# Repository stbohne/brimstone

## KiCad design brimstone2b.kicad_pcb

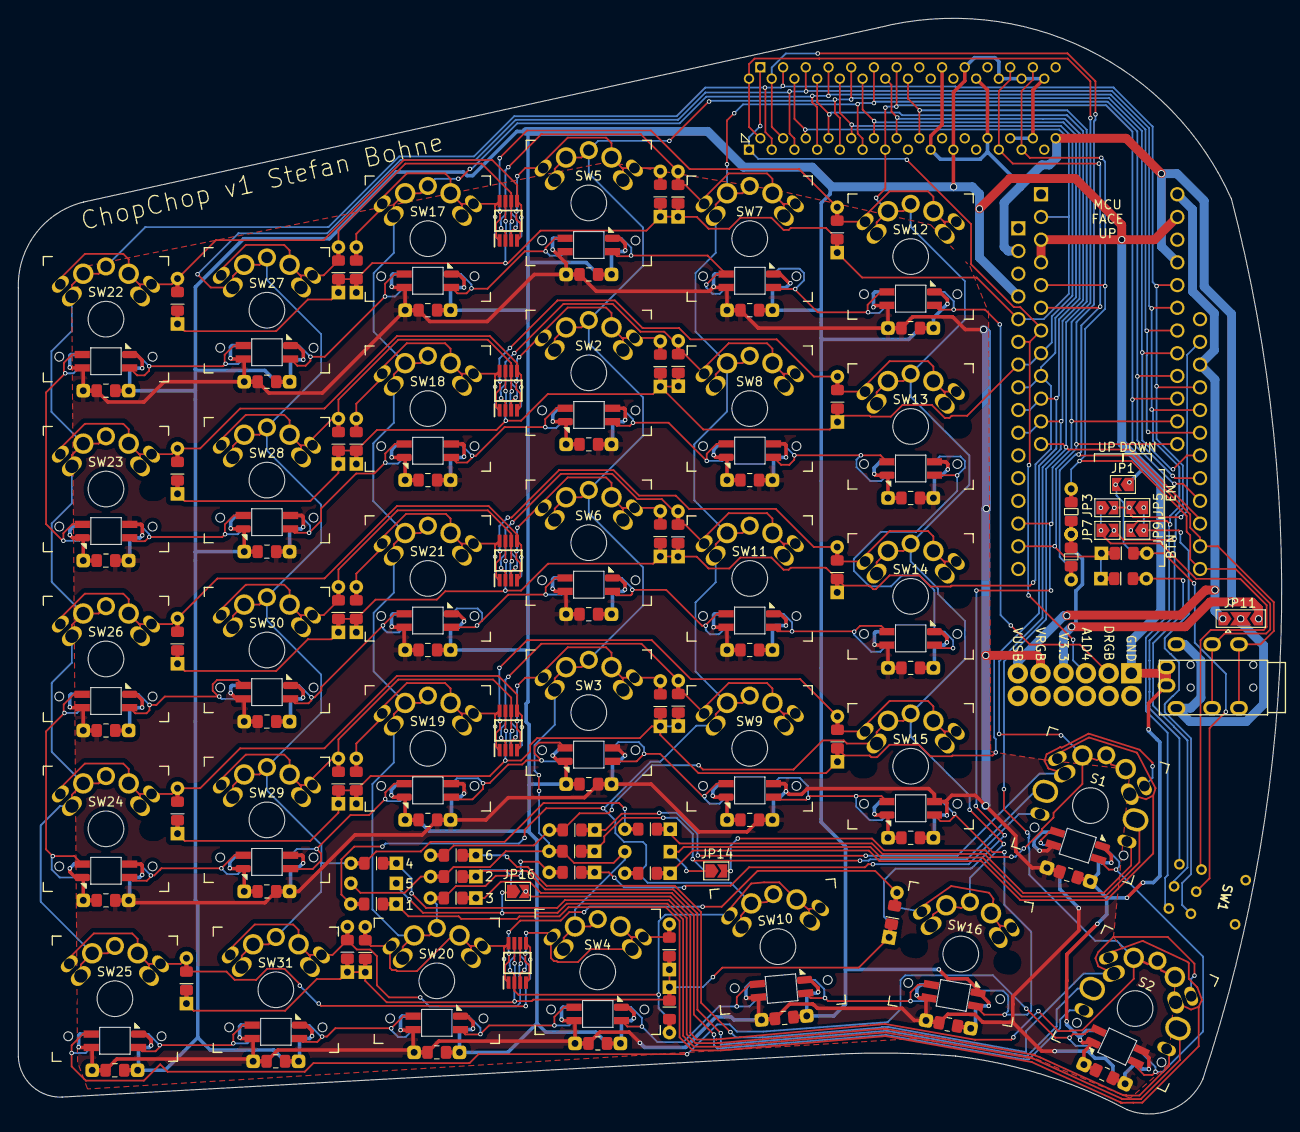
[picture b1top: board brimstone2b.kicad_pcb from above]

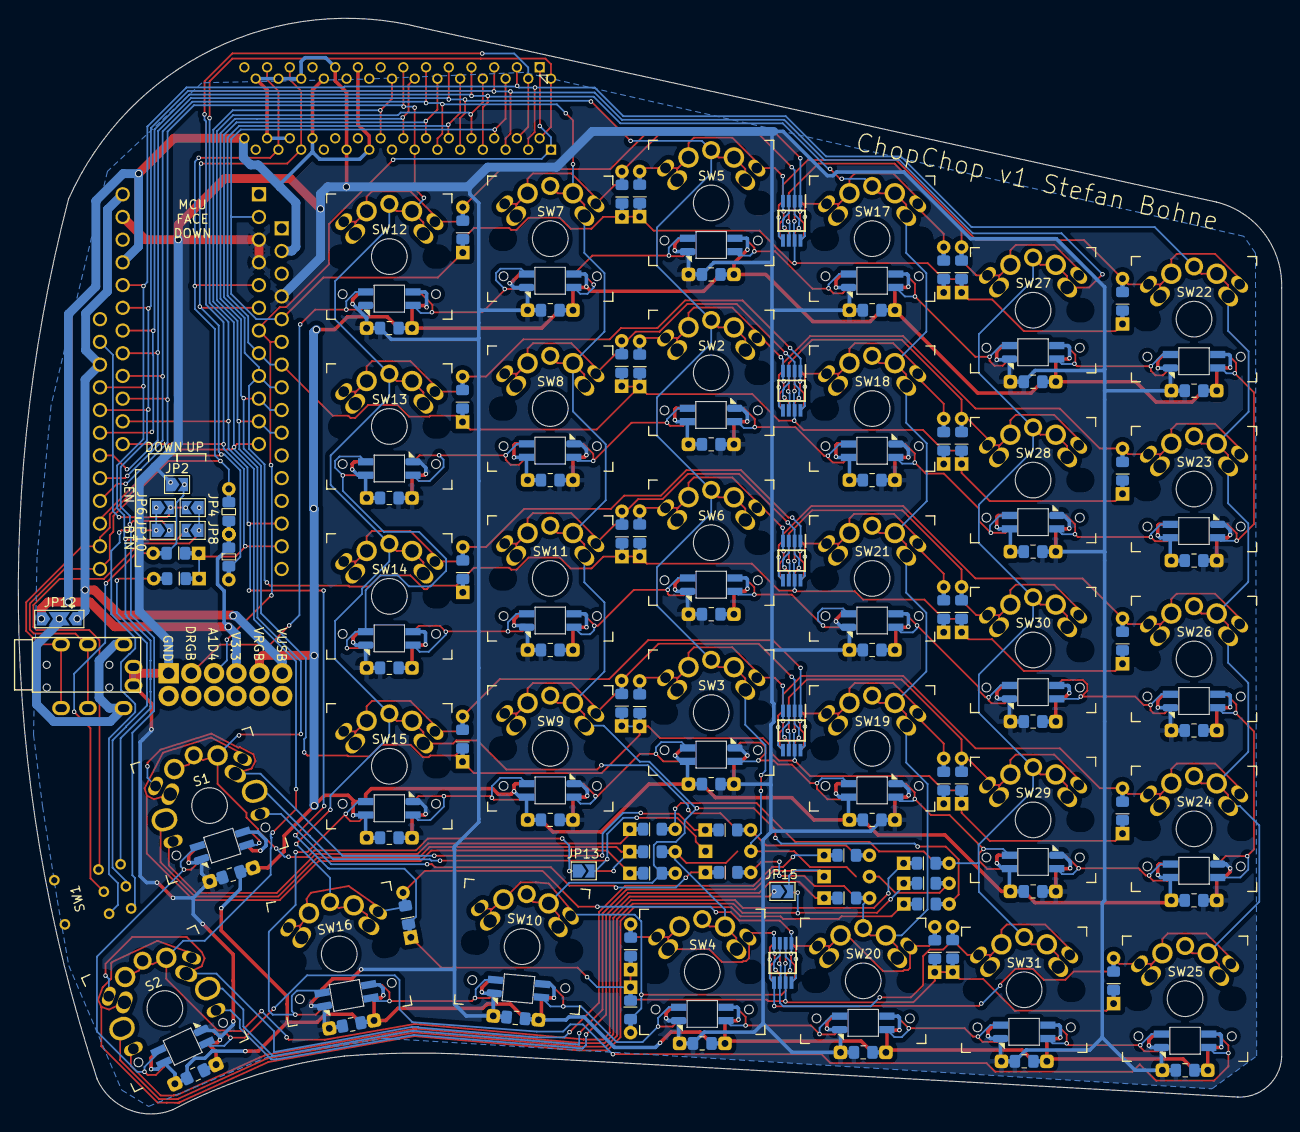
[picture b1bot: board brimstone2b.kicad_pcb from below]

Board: 2 copper layers, 141.3 x 122.5 mm, 171 parts (17 on the bottom side), 101 nets.

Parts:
C1, C2, C3, C4, C5, C6, C7, C8, C9, C10, C11, C12, C13, C14, C15, C16, C17, C18, C19, C20, C21, C22, C23, C24, C25, C26, C27, C28, C29, C30, C31, C32: 100nF; C_0805_2012Metric_Pad1.18x1.45mm_HandSolder_Dual_Reversible
D1, D2, D4, D5, D7, D8, D11, D12, D14, D15, D17, D19, D21, D23, D25, D27, D29, D31, D33, D35, D37, D39, D41, D43, D45, D47, D49, D51, D53, D55, D57, D59, D61, D63, D65, D67, D69, D71, D73, D75: D; D_0805_2012Metric_Pad1.18x1.45mm_HandSolder_Dual_Reversible
D3, D9, D10, D16: D; D_0805_2012Metric_Pad1.18x1.45mm_HandSolder_Dual
D101, D102, D103, D104, D105, D106, D107, D108, D109, D110, D111, D112, D113, D114, D115, D116, D117, D118, D119, D120, D121, D122, D123, D124, D125, D126, D127, D128, D129, D130, D131, D132: SK6812MINI2; SK6812-MINI-E_Reversible
IC1, IC2: MCP23017-E_SP; DIP794W56P254L3486H508Q28N
IC3, IC4, IC5, IC6, IC7: PACDN006MR; SOP65P490X110-8N-reversible
JP1, JP2, JP3, JP4, JP5, JP6, JP7, JP8, JP9, JP10, JP13, JP14, JP15, JP16: SolderJumper_2_Open; SolderJumper-2_P1.3mm_Open_TrianglePad1.0x1.5mm
JP11, JP12: Jumper_3_Bridged12; SolderJumper-3_P2.0mm_Open_TrianglePad1.0x1.5mm
R1, R2: 4.7k; R_0805_2012Metric_Pad1.18x1.45mm_HandSolder_Dual_Reversible
S1, S2: 2/5SW; SW_MX_PG1350_SKQU_reversible
SW1: SW_Push_DPDT; A9TS220012
SW2, SW3, SW4, SW5, SW6, SW7, SW8, SW9, SW10, SW11, SW12, SW13, SW14, SW15, SW16, SW17, SW18, SW19, SW20, SW21, SW22, SW23, SW24, SW25, SW26, SW27, SW28, SW29, SW30, SW31: SW_Push; SW_MX_PG1350_reversible
U1: Testarea
U2: Adafruit_Feather_32u4_BluefruitLE; Adafruit_Feather
U3: ProMicro; ProMicro-NoSilk
U4, U5: TRRS; TRRS-PJ-320A

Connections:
+3V3: IC1.9 (VDD), IC1.18 (~RESET), IC2.9 (VDD), IC2.15 (A0), IC2.18 (~RESET), JP11.3 (B), JP12.3 (B), R1.1, R2.1, U1.4 (V33), U2.2 (3V3), U3.21 (VCC)
+5V: JP11.1 (A), JP12.1 (A), U1.6 (VUSB), U2.26 (USB), U3.24 (RAW)
/Row1/DOUT: D114.4 (DIN), D123.2 (DOUT)
/Row1/Key30/DIN: D106.4 (DIN), D108.2 (DOUT)
/Row1/Key30/DOUT: D106.2 (DOUT), D118.4 (DIN)
/Row1/Key30/ROWD: D23.2 (A), IC7.4 (CH3), SW5.2
/Row1/Key31/DIN: D108.4 (DIN), D113.2 (DOUT)
/Row1/Key31/ROWD: D27.2 (A), IC7.2 (CH2), SW7.2
/Row1/Key32/ROWD: D37.2 (A), IC7.1 (CH1), SW12.2
/Row1/Key33/DOUT: D118.2 (DOUT), D128.4 (DIN)
/Row1/Key33/ROWD: D47.2 (A), IC7.8 (CH6), SW17.2
/Row1/Key34/DIN: D123.4 (DIN), D128.2 (DOUT)
/Row1/Key34/ROWD: D57.2 (A), IC7.5 (CH4), SW22.2
/Row1/Key35/ROWD: D67.2 (A), IC7.6 (CH5), SW27.2
/Row2/DOUT: D115.4 (DIN), D124.2 (DOUT)
/Row2/Key30/DIN: D103.4 (DIN), D109.2 (DOUT)
/Row2/Key30/DOUT: D103.2 (DOUT), D119.4 (DIN)
/Row2/Key30/ROWD: D17.2 (A), IC3.4 (CH3), SW2.2
/Row2/Key31/DIN: D109.4 (DIN), D114.2 (DOUT)
/Row2/Key31/ROWD: D29.2 (A), IC3.2 (CH2), SW8.2
/Row2/Key32/ROWD: D39.2 (A), IC3.1 (CH1), SW13.2
/Row2/Key33/DOUT: D119.2 (DOUT), D129.4 (DIN)
/Row2/Key33/ROWD: D49.2 (A), IC3.8 (CH6), SW18.2
/Row2/Key34/DIN: D124.4 (DIN), D129.2 (DOUT)
/Row2/Key34/ROWD: D59.2 (A), IC3.5 (CH4), SW23.2
/Row2/Key35/ROWD: D69.2 (A), IC3.6 (CH5), SW28.2
/Row3/DOUT: D116.4 (DIN), D127.2 (DOUT)
/Row3/Key30/DIN: D107.4 (DIN), D112.2 (DOUT)
/Row3/Key30/DOUT: D107.2 (DOUT), D122.4 (DIN)
/Row3/Key30/ROWD: D25.2 (A), IC4.4 (CH3), SW6.2
/Row3/Key31/DIN: D112.4 (DIN), D115.2 (DOUT)
/Row3/Key31/ROWD: D35.2 (A), IC4.2 (CH2), SW11.2
/Row3/Key32/ROWD: D41.2 (A), IC4.1 (CH1), SW14.2
/Row3/Key33/DOUT: D122.2 (DOUT), D131.4 (DIN)
/Row3/Key33/ROWD: D55.2 (A), IC4.8 (CH6), SW21.2
/Row3/Key34/DIN: D127.4 (DIN), D131.2 (DOUT)
/Row3/Key34/ROWD: D65.2 (A), IC4.5 (CH4), SW26.2
/Row3/Key35/ROWD: D73.2 (A), IC4.6 (CH5), SW30.2
/Row4/DOUT: D117.4 (DIN), D125.2 (DOUT)
/Row4/Key30/DIN: D104.4 (DIN), D110.2 (DOUT)
/Row4/Key30/DOUT: D104.2 (DOUT), D120.4 (DIN)
/Row4/Key30/ROWD: D19.2 (A), IC5.4 (CH3), SW3.2
/Row4/Key31/DIN: D110.4 (DIN), D116.2 (DOUT)
/Row4/Key31/ROWD: D31.2 (A), IC5.2 (CH2), SW9.2
/Row4/Key32/ROWD: D43.2 (A), IC5.1 (CH1), SW15.2
/Row4/Key33/DOUT: D120.2 (DOUT), D130.4 (DIN)
/Row4/Key33/ROWD: D51.2 (A), IC5.8 (CH6), SW19.2
/Row4/Key34/DIN: D125.4 (DIN), D130.2 (DOUT)
/Row4/Key34/ROWD: D61.2 (A), IC5.5 (CH4), SW24.2
/Row4/Key35/ROWD: D71.2 (A), IC5.6 (CH5), SW29.2
/Row5/DOUT: D102.4 (DIN), D126.2 (DOUT)
/Row5/Key30/DIN: D105.4 (DIN), D111.2 (DOUT)
/Row5/Key30/DOUT: D105.2 (DOUT), D121.4 (DIN)
/Row5/Key30/ROWD: D21.2 (A), IC6.4 (CH3), SW4.2
/Row5/Key31/DIN: D111.4 (DIN), D117.2 (DOUT)
/Row5/Key31/ROWD: D33.2 (A), IC6.2 (CH2), SW10.2
/Row5/Key32/ROWD: D45.2 (A), IC6.1 (CH1), SW16.2
/Row5/Key33/DOUT: D121.2 (DOUT), D132.4 (DIN)
/Row5/Key33/ROWD: D53.2 (A), IC6.8 (CH6), SW20.2
/Row5/Key34/DIN: D126.4 (DIN), D132.2 (DOUT)
/Row5/Key34/ROWD: D63.2 (A), IC6.5 (CH4), SW25.2
/Row5/Key35/ROWD: D75.2 (A), IC6.6 (CH5), SW31.2
/key5way/DOUT: D101.4 (DIN), D102.2 (DOUT)
COL1: IC1.2 (GPB1), IC2.2 (GPB1), JP7.2 (B), JP8.2 (B), SW1.4 (A), SW22.1, SW23.1, SW24.1, SW25.1, SW26.1, U2.25 (D13), U3.20 (F4)
COL2: D8.2 (A), D15.2 (A), IC1.3 (GPB2), IC2.3 (GPB2), JP9.2 (B), JP10.2 (B), SW1.6 (C), SW27.1, SW28.1, SW29.1, SW30.1, SW31.1, U2.24 (D12), U3.19 (F5)
COL3: D5.2 (A), D12.2 (A), IC1.4 (GPB3), IC2.4 (GPB3), SW17.1, SW18.1, SW19.1, SW20.1, SW21.1, U2.23 (D11), U3.18 (F6)
COL4: D3.2 (A), D9.2 (A), D10.2 (A), D16.2 (A), IC1.5 (GPB4), IC2.5 (GPB4), SW2.1, SW3.1, SW4.1, SW5.1, SW6.1, U2.22 (D10), U3.17 (F7)
COL5: D4.2 (A), D11.2 (A), IC1.6 (GPB5), IC2.6 (GPB5), SW7.1, SW8.1, SW9.1, SW10.1, SW11.1, U2.21 (D9), U3.16 (B1)
COL6: D7.2 (A), D14.2 (A), IC1.7 (GPB6), IC2.7 (GPB6), SW12.1, SW13.1, SW14.1, SW15.1, SW16.1, U2.20 (D6), U3.15 (B3)
DRGB: D113.4 (DIN), U1.2 (DRGB)
EN: JP3.2 (B), JP4.2 (B), JP5.2 (B), JP6.2 (B), U2.27 (EN)
GND: C1.2, C2.2, C3.2, C4.2, C5.2, C6.2, C7.2, C8.2, C9.2, C10.2, C11.2, C12.2, C13.2, C14.2, C15.2, C16.2, C17.2, C18.2, C19.2, C20.2, C21.2, C22.2, C23.2, C24.2, C25.2, C26.2, C27.2, C28.2, C29.2, C30.2, C31.2, C32.2, D101.3 (VSS), D102.3 (VSS), D103.3 (VSS), D104.3 (VSS), D105.3 (VSS), D106.3 (VSS), D107.3 (VSS), D108.3 (VSS), D109.3 (VSS), D110.3 (VSS), D111.3 (VSS), D112.3 (VSS), D113.3 (VSS), D114.3 (VSS), D115.3 (VSS), D116.3 (VSS), D117.3 (VSS), D118.3 (VSS), D119.3 (VSS), D120.3 (VSS), D121.3 (VSS), D122.3 (VSS), D123.3 (VSS), D124.3 (VSS), D125.3 (VSS), D126.3 (VSS), D127.3 (VSS), D128.3 (VSS), D129.3 (VSS), D130.3 (VSS), D131.3 (VSS), D132.3 (VSS), IC1.10 (VSS), IC1.15 (A0), IC1.16 (A1), IC1.17 (A2), IC2.10 (VSS), IC2.16 (A1), IC2.17 (A2), JP1.1 (A), JP2.1 (A), U1.1 (GND), U2.4 (GND), U3.3 (GND), U3.4 (GND), U3.23 (GND), U4.1 (SLEEVE), U5.1 (SLEEVE)
LED_DIN: IC1.1 (GPB0), IC2.1 (GPB0), U1.3 (A1D4), U2.6 (A1), U3.7 (D4)
unnamed: D1.2 (A), JP1.2 (B), JP2.2 (B), SW1.2 (B)
unnamed: D2.2 (A), SW1.5 (B)
unnamed: D3.1 (K), JP13.2 (B), S1.2
unnamed: D4.1 (K), S1.1
unnamed: D5.1 (K), S1.3
unnamed: D7.1 (K), S1.6
unnamed: D8.1 (K), S1.4
unnamed: D9.1 (K), JP14.1 (A), S1.5
unnamed: D10.1 (K), JP15.2 (B), S2.2
unnamed: D11.1 (K), S2.1
unnamed: D12.1 (K), S2.3
unnamed: D14.1 (K), S2.6
unnamed: D15.1 (K), S2.4
unnamed: D16.1 (K), JP16.1 (A), S2.5
unnamed: JP3.1 (A), JP4.1 (A), JP7.1 (A), JP8.1 (A), SW1.1 (A)
unnamed: JP5.1 (A), JP6.1 (A), JP9.1 (A), JP10.1 (A), SW1.3 (C)
unnamed: JP11.2 (C), JP12.2 (C), U4.2 (TIP), U5.2 (TIP)
ROW1: D23.1 (K), D27.1 (K), D37.1 (K), D47.1 (K), D57.1 (K), D67.1 (K), IC1.26 (GPA5), IC2.26 (GPA5), IC7.7 (VP), U2.5 (A0), U3.2 (RX)
ROW2: D17.1 (K), D29.1 (K), D39.1 (K), D49.1 (K), D59.1 (K), D69.1 (K), IC1.24 (GPA3), IC2.24 (GPA3), IC3.7 (VP), U2.7 (A2), U3.8 (C6)
ROW3: D25.1 (K), D35.1 (K), D41.1 (K), D55.1 (K), D65.1 (K), D73.1 (K), IC1.23 (GPA2), IC2.23 (GPA2), IC4.7 (VP), U2.8 (A3), U3.9 (D7)
ROW4: D19.1 (K), D31.1 (K), D43.1 (K), D51.1 (K), D61.1 (K), D71.1 (K), IC1.22 (GPA1), IC2.22 (GPA1), IC5.7 (VP), U2.9 (A4), U3.10 (E6)
ROW5: D21.1 (K), D33.1 (K), D45.1 (K), D53.1 (K), D63.1 (K), D75.1 (K), IC1.28 (GPA7), IC2.28 (GPA7), IC6.7 (VP), U2.14 (RX/D0), U3.14 (B2)
ROW6: D1.1 (K), D2.1 (K), IC1.27 (GPA6), IC2.27 (GPA6), U2.15 (TX/D1), U3.13 (B6)
ROW7: IC1.21 (GPA0), IC2.21 (GPA0), JP15.1 (A), JP16.2 (B), S2.7, U2.19 (D5), U3.12 (B5)
ROW8: IC1.25 (GPA4), IC2.25 (GPA4), JP13.1 (A), JP14.2 (B), S1.7, U2.10 (A5), U3.11 (B4)
SCL: IC1.12 (SCL), IC2.12 (SCL), R2.2, U2.18 (SCL/D3), U3.6 (SCL), U4.4 (RING2), U5.4 (RING2)
SDA: IC1.13 (SDA), IC2.13 (SDA), R1.2, U2.17 (SDA/D2), U3.5 (SDA), U4.3 (RING1), U5.3 (RING1)
VRGB: C1.1, C2.1, C3.1, C4.1, C5.1, C6.1, C7.1, C8.1, C9.1, C10.1, C11.1, C12.1, C13.1, C14.1, C15.1, C16.1, C17.1, C18.1, C19.1, C20.1, C21.1, C22.1, C23.1, C24.1, C25.1, C26.1, C27.1, C28.1, C29.1, C30.1, C31.1, C32.1, D101.1 (VDD), D102.1 (VDD), D103.1 (VDD), D104.1 (VDD), D105.1 (VDD), D106.1 (VDD), D107.1 (VDD), D108.1 (VDD), D109.1 (VDD), D110.1 (VDD), D111.1 (VDD), D112.1 (VDD), D113.1 (VDD), D114.1 (VDD), D115.1 (VDD), D116.1 (VDD), D117.1 (VDD), D118.1 (VDD), D119.1 (VDD), D120.1 (VDD), D121.1 (VDD), D122.1 (VDD), D123.1 (VDD), D124.1 (VDD), D125.1 (VDD), D126.1 (VDD), D127.1 (VDD), D128.1 (VDD), D129.1 (VDD), D130.1 (VDD), D131.1 (VDD), D132.1 (VDD), U1.5 (VRGB)

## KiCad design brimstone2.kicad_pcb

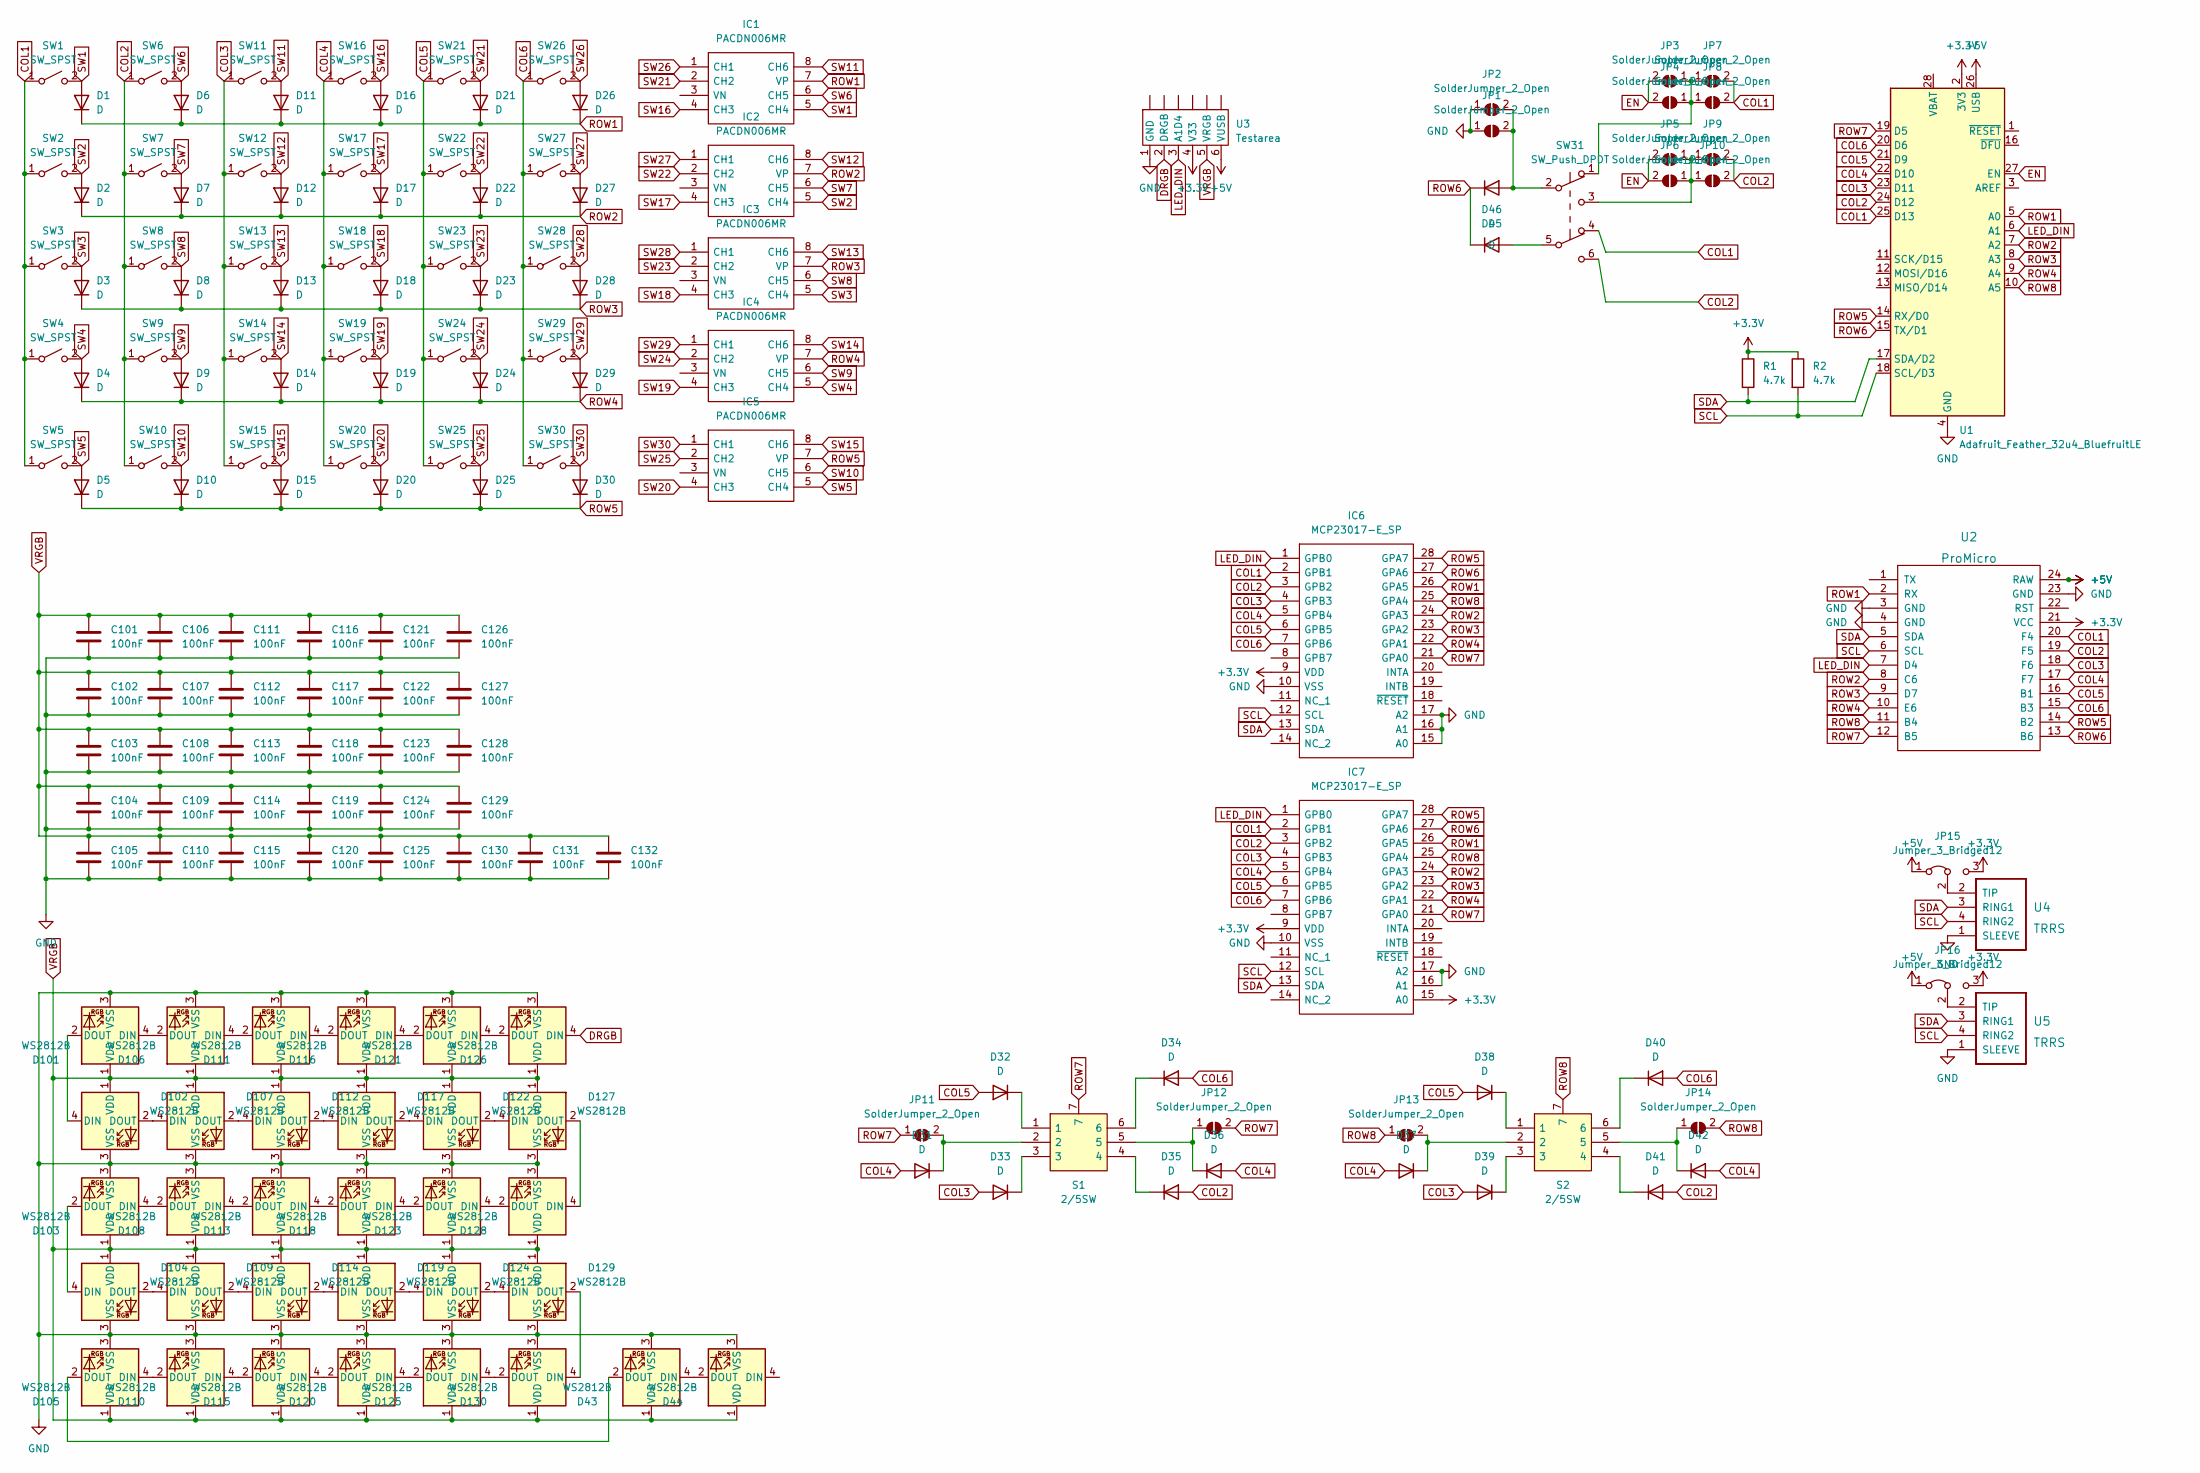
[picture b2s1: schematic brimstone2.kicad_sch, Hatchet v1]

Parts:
C101, C102, C103, C104, C105, C106, C107, C108, C109, C110, C111, C112, C113, C114, C115, C116, C117, C118, C119, C120, C121, C122, C123, C124, C125, C126, C127, C128, C129, C130, C131, C132: 100nF; C_0805_2012Metric_Pad1.18x1.45mm_HandSolder_Dual_Reversible
D1, D2, D3, D4, D5, D6, D7, D8, D9, D10, D11, D12, D13, D14, D15, D16, D17, D18, D19, D20, D21, D22, D23, D24, D25, D26, D27, D28, D29, D30, D32, D33, D34, D35, D38, D39, D40, D41, D45, D46: D; D_0805_2012Metric_Pad1.18x1.45mm_HandSolder_Dual_Reversible
D31, D36, D37, D42: D; D_0805_2012Metric_Pad1.18x1.45mm_HandSolder_Dual
D43, D44, D101, D102, D103, D104, D105, D106, D107, D108, D109, D110, D111, D112, D113, D114, D115, D116, D117, D118, D119, D120, D121, D122, D123, D124, D125, D126, D127, D128, D129, D130: WS2812B; SK6812-MINI-E_Reversible
IC1, IC2, IC3, IC4, IC5: PACDN006MR; SOP65P490X110-8N-reversible; Mouser Part Number 748-PACDN006MR
IC6, IC7: MCP23017-E_SP; DIP794W56P254L3486H508Q28N; Mouser Part Number 579-MCP23017-E/SP
JP1, JP2, JP3, JP4, JP5, JP6, JP7, JP8, JP9, JP10, JP11, JP12, JP13, JP14: SolderJumper_2_Open; SolderJumper-2_P1.3mm_Open_TrianglePad1.0x1.5mm
JP15, JP16: Jumper_3_Bridged12; SolderJumper-3_P2.0mm_Open_TrianglePad1.0x1.5mm
R1, R2: 4.7k; R_0805_2012Metric_Pad1.18x1.45mm_HandSolder_Dual_Reversible
S1, S2: 2/5SW; SW_MX_PG1350_SKQU_reversible; Mouser Part Number 688-SKQUCA
SW1, SW2, SW3, SW4, SW5, SW6, SW7, SW8, SW9, SW10, SW11, SW12, SW13, SW14, SW15, SW16, SW17, SW18, SW19, SW20, SW21, SW22, SW23, SW24, SW25, SW26, SW27, SW28, SW29, SW30: SW_SPST; SW_MX_PG1350_reversible
SW31: SW_Push_DPDT; A9TS220012
U1: Adafruit_Feather_32u4_BluefruitLE; Adafruit_Feather
U2: ProMicro; ProMicro-NoSilk
U3: Testarea
U4, U5: TRRS; TRRS-PJ-320A

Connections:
+3V3: IC6.9 (VDD), IC7.9 (VDD), IC7.15 (A0), JP15.3 (B), JP16.3 (B), R1.1, R2.1, U1.2 (3V3), U2.21 (VCC), U3.4 (V33)
+5V: JP15.1 (A), JP16.1 (A), U1.26 (USB), U2.24 (RAW), U3.6 (VUSB)
COL1: IC6.2 (GPB1), IC7.2 (GPB1), JP7.2 (B), JP8.2 (B), SW1.1 (A), SW2.1 (A), SW3.1 (A), SW4.1 (A), SW5.1 (A), SW31.4 (A), U1.25 (D13), U2.20 (F4)
COL2: D35.2 (A), D41.2 (A), IC6.3 (GPB2), IC7.3 (GPB2), JP9.2 (B), JP10.2 (B), SW6.1 (A), SW7.1 (A), SW8.1 (A), SW9.1 (A), SW10.1 (A), SW31.6 (C), U1.24 (D12), U2.19 (F5)
COL3: D33.2 (A), D39.2 (A), IC6.4 (GPB3), IC7.4 (GPB3), SW11.1 (A), SW12.1 (A), SW13.1 (A), SW14.1 (A), SW15.1 (A), U1.23 (D11), U2.18 (F6)
COL4: D31.2 (A), D36.2 (A), D37.2 (A), D42.2 (A), IC6.5 (GPB4), IC7.5 (GPB4), SW16.1 (A), SW17.1 (A), SW18.1 (A), SW19.1 (A), SW20.1 (A), U1.22 (D10), U2.17 (F7)
COL5: D32.2 (A), D38.2 (A), IC6.6 (GPB5), IC7.6 (GPB5), SW21.1 (A), SW22.1 (A), SW23.1 (A), SW24.1 (A), SW25.1 (A), U1.21 (D9), U2.16 (B1)
COL6: D34.2 (A), D40.2 (A), IC6.7 (GPB6), IC7.7 (GPB6), SW26.1 (A), SW27.1 (A), SW28.1 (A), SW29.1 (A), SW30.1 (A), U1.20 (D6), U2.15 (B3)
DRGB: D126.4 (DIN), U3.2 (DRGB)
EN: JP3.2 (B), JP4.2 (B), JP5.2 (B), JP6.2 (B), U1.27 (EN)
GND: C101.2, C102.2, C103.2, C104.2, C105.2, C106.2, C107.2, C108.2, C109.2, C110.2, C111.2, C112.2, C113.2, C114.2, C115.2, C116.2, C117.2, C118.2, C119.2, C120.2, C121.2, C122.2, C123.2, C124.2, C125.2, C126.2, C127.2, C128.2, C129.2, C130.2, C131.2, C132.2, D43.3 (VSS), D44.3 (VSS), D101.3 (VSS), D102.3 (VSS), D103.3 (VSS), D104.3 (VSS), D105.3 (VSS), D106.3 (VSS), D107.3 (VSS), D108.3 (VSS), D109.3 (VSS), D110.3 (VSS), D111.3 (VSS), D112.3 (VSS), D113.3 (VSS), D114.3 (VSS), D115.3 (VSS), D116.3 (VSS), D117.3 (VSS), D118.3 (VSS), D119.3 (VSS), D120.3 (VSS), D121.3 (VSS), D122.3 (VSS), D123.3 (VSS), D124.3 (VSS), D125.3 (VSS), D126.3 (VSS), D127.3 (VSS), D128.3 (VSS), D129.3 (VSS), D130.3 (VSS), IC6.10 (VSS), IC6.15 (A0), IC6.16 (A1), IC6.17 (A2), IC7.10 (VSS), IC7.16 (A1), IC7.17 (A2), JP1.1 (A), JP2.1 (A), U1.4 (GND), U2.3 (GND), U2.4 (GND), U2.23 (GND), U3.1 (GND), U4.1 (SLEEVE), U5.1 (SLEEVE)
LED_DIN: IC6.1 (GPB0), IC7.1 (GPB0), U1.6 (A1), U2.7 (D4), U3.3 (A1D4)
unnamed: D31.1 (K), JP11.2 (B), S1.2
unnamed: D32.1 (K), S1.1
unnamed: D33.1 (K), S1.3
unnamed: D34.1 (K), S1.6
unnamed: D35.1 (K), S1.4
unnamed: D36.1 (K), JP12.1 (A), S1.5
unnamed: D37.1 (K), JP13.2 (B), S2.2
unnamed: D38.1 (K), S2.1
unnamed: D39.1 (K), S2.3
unnamed: D40.1 (K), S2.6
unnamed: D41.1 (K), S2.4
unnamed: D42.1 (K), JP14.1 (A), S2.5
unnamed: D43.4 (DIN), D44.2 (DOUT)
unnamed: D45.2 (A), JP1.2 (B), JP2.2 (B), SW31.2 (B)
unnamed: D46.2 (A), SW31.5 (B)
unnamed: D101.2 (DOUT), D102.4 (DIN)
unnamed: D101.4 (DIN), D106.2 (DOUT)
unnamed: D102.2 (DOUT), D107.4 (DIN)
unnamed: D103.2 (DOUT), D104.4 (DIN)
unnamed: D103.4 (DIN), D108.2 (DOUT)
unnamed: D104.2 (DOUT), D109.4 (DIN)
unnamed: D43.2 (DOUT), D105.2 (DOUT)
unnamed: D105.4 (DIN), D110.2 (DOUT)
unnamed: D106.4 (DIN), D111.2 (DOUT)
unnamed: D107.2 (DOUT), D112.4 (DIN)
unnamed: D108.4 (DIN), D113.2 (DOUT)
unnamed: D109.2 (DOUT), D114.4 (DIN)
unnamed: D110.4 (DIN), D115.2 (DOUT)
unnamed: D111.4 (DIN), D116.2 (DOUT)
unnamed: D112.2 (DOUT), D117.4 (DIN)
unnamed: D113.4 (DIN), D118.2 (DOUT)
unnamed: D114.2 (DOUT), D119.4 (DIN)
unnamed: D115.4 (DIN), D120.2 (DOUT)
unnamed: D116.4 (DIN), D121.2 (DOUT)
unnamed: D117.2 (DOUT), D122.4 (DIN)
unnamed: D118.4 (DIN), D123.2 (DOUT)
unnamed: D119.2 (DOUT), D124.4 (DIN)
unnamed: D120.4 (DIN), D125.2 (DOUT)
unnamed: D121.4 (DIN), D126.2 (DOUT)
unnamed: D122.2 (DOUT), D127.4 (DIN)
unnamed: D123.4 (DIN), D128.2 (DOUT)
unnamed: D124.2 (DOUT), D129.4 (DIN)
unnamed: D125.4 (DIN), D130.2 (DOUT)
unnamed: D127.2 (DOUT), D128.4 (DIN)
unnamed: D129.2 (DOUT), D130.4 (DIN)
unnamed: JP3.1 (A), JP4.1 (A), JP7.1 (A), JP8.1 (A), SW31.1 (A)
unnamed: JP5.1 (A), JP6.1 (A), JP9.1 (A), JP10.1 (A), SW31.3 (C)
unnamed: JP15.2 (C), U4.2 (TIP)
unnamed: JP16.2 (C), U5.2 (TIP)
ROW1: D1.1 (K), D6.1 (K), D11.1 (K), D16.1 (K), D21.1 (K), D26.1 (K), IC1.7 (VP), IC6.26 (GPA5), IC7.26 (GPA5), U1.5 (A0), U2.2 (RX)
ROW2: D2.1 (K), D7.1 (K), D12.1 (K), D17.1 (K), D22.1 (K), D27.1 (K), IC2.7 (VP), IC6.24 (GPA3), IC7.24 (GPA3), U1.7 (A2), U2.8 (C6)
ROW3: D3.1 (K), D8.1 (K), D13.1 (K), D18.1 (K), D23.1 (K), D28.1 (K), IC3.7 (VP), IC6.23 (GPA2), IC7.23 (GPA2), U1.8 (A3), U2.9 (D7)
ROW4: D4.1 (K), D9.1 (K), D14.1 (K), D19.1 (K), D24.1 (K), D29.1 (K), IC4.7 (VP), IC6.22 (GPA1), IC7.22 (GPA1), U1.9 (A4), U2.10 (E6)
ROW5: D5.1 (K), D10.1 (K), D15.1 (K), D20.1 (K), D25.1 (K), D30.1 (K), IC5.7 (VP), IC6.28 (GPA7), IC7.28 (GPA7), U1.14 (RX/D0), U2.14 (B2)
ROW6: D45.1 (K), D46.1 (K), IC6.27 (GPA6), IC7.27 (GPA6), U1.15 (TX/D1), U2.13 (B6)
ROW7: IC6.21 (GPA0), IC7.21 (GPA0), JP11.1 (A), JP12.2 (B), S1.7, U1.19 (D5), U2.12 (B5)
ROW8: IC6.25 (GPA4), IC7.25 (GPA4), JP13.1 (A), JP14.2 (B), S2.7, U1.10 (A5), U2.11 (B4)
SCL: IC6.12 (SCL), IC7.12 (SCL), R2.2, U1.18 (SCL/D3), U2.6 (SCL), U4.4 (RING2), U5.4 (RING2)
SDA: IC6.13 (SDA), IC7.13 (SDA), R1.2, U1.17 (SDA/D2), U2.5 (SDA), U4.3 (RING1), U5.3 (RING1)
SW1: D1.2 (A), IC1.5 (CH4), SW1.2 (B)
SW2: D2.2 (A), IC2.5 (CH4), SW2.2 (B)
SW3: D3.2 (A), IC3.5 (CH4), SW3.2 (B)
SW4: D4.2 (A), IC4.5 (CH4), SW4.2 (B)
SW5: D5.2 (A), IC5.5 (CH4), SW5.2 (B)
SW6: D6.2 (A), IC1.6 (CH5), SW6.2 (B)
SW7: D7.2 (A), IC2.6 (CH5), SW7.2 (B)
SW8: D8.2 (A), IC3.6 (CH5), SW8.2 (B)
SW9: D9.2 (A), IC4.6 (CH5), SW9.2 (B)
SW10: D10.2 (A), IC5.6 (CH5), SW10.2 (B)
SW11: D11.2 (A), IC1.8 (CH6), SW11.2 (B)
SW12: D12.2 (A), IC2.8 (CH6), SW12.2 (B)
SW13: D13.2 (A), IC3.8 (CH6), SW13.2 (B)
SW14: D14.2 (A), IC4.8 (CH6), SW14.2 (B)
SW15: D15.2 (A), IC5.8 (CH6), SW15.2 (B)
SW16: D16.2 (A), IC1.4 (CH3), SW16.2 (B)
SW17: D17.2 (A), IC2.4 (CH3), SW17.2 (B)
SW18: D18.2 (A), IC3.4 (CH3), SW18.2 (B)
SW19: D19.2 (A), IC4.4 (CH3), SW19.2 (B)
SW20: D20.2 (A), IC5.4 (CH3), SW20.2 (B)
SW21: D21.2 (A), IC1.2 (CH2), SW21.2 (B)
SW22: D22.2 (A), IC2.2 (CH2), SW22.2 (B)
SW23: D23.2 (A), IC3.2 (CH2), SW23.2 (B)
SW24: D24.2 (A), IC4.2 (CH2), SW24.2 (B)
SW25: D25.2 (A), IC5.2 (CH2), SW25.2 (B)
SW26: D26.2 (A), IC1.1 (CH1), SW26.2 (B)
SW27: D27.2 (A), IC2.1 (CH1), SW27.2 (B)
SW28: D28.2 (A), IC3.1 (CH1), SW28.2 (B)
SW29: D29.2 (A), IC4.1 (CH1), SW29.2 (B)
SW30: D30.2 (A), IC5.1 (CH1), SW30.2 (B)
VRGB: C101.1, C102.1, C103.1, C104.1, C105.1, C106.1, C107.1, C108.1, C109.1, C110.1, C111.1, C112.1, C113.1, C114.1, C115.1, C116.1, C117.1, C118.1, C119.1, C120.1, C121.1, C122.1, C123.1, C124.1, C125.1, C126.1, C127.1, C128.1, C129.1, C130.1, C131.1, C132.1, D43.1 (VDD), D44.1 (VDD), D101.1 (VDD), D102.1 (VDD), D103.1 (VDD), D104.1 (VDD), D105.1 (VDD), D106.1 (VDD), D107.1 (VDD), D108.1 (VDD), D109.1 (VDD), D110.1 (VDD), D111.1 (VDD), D112.1 (VDD), D113.1 (VDD), D114.1 (VDD), D115.1 (VDD), D116.1 (VDD), D117.1 (VDD), D118.1 (VDD), D119.1 (VDD), D120.1 (VDD), D121.1 (VDD), D122.1 (VDD), D123.1 (VDD), D124.1 (VDD), D125.1 (VDD), D126.1 (VDD), D127.1 (VDD), D128.1 (VDD), D129.1 (VDD), D130.1 (VDD), U3.5 (VRGB)

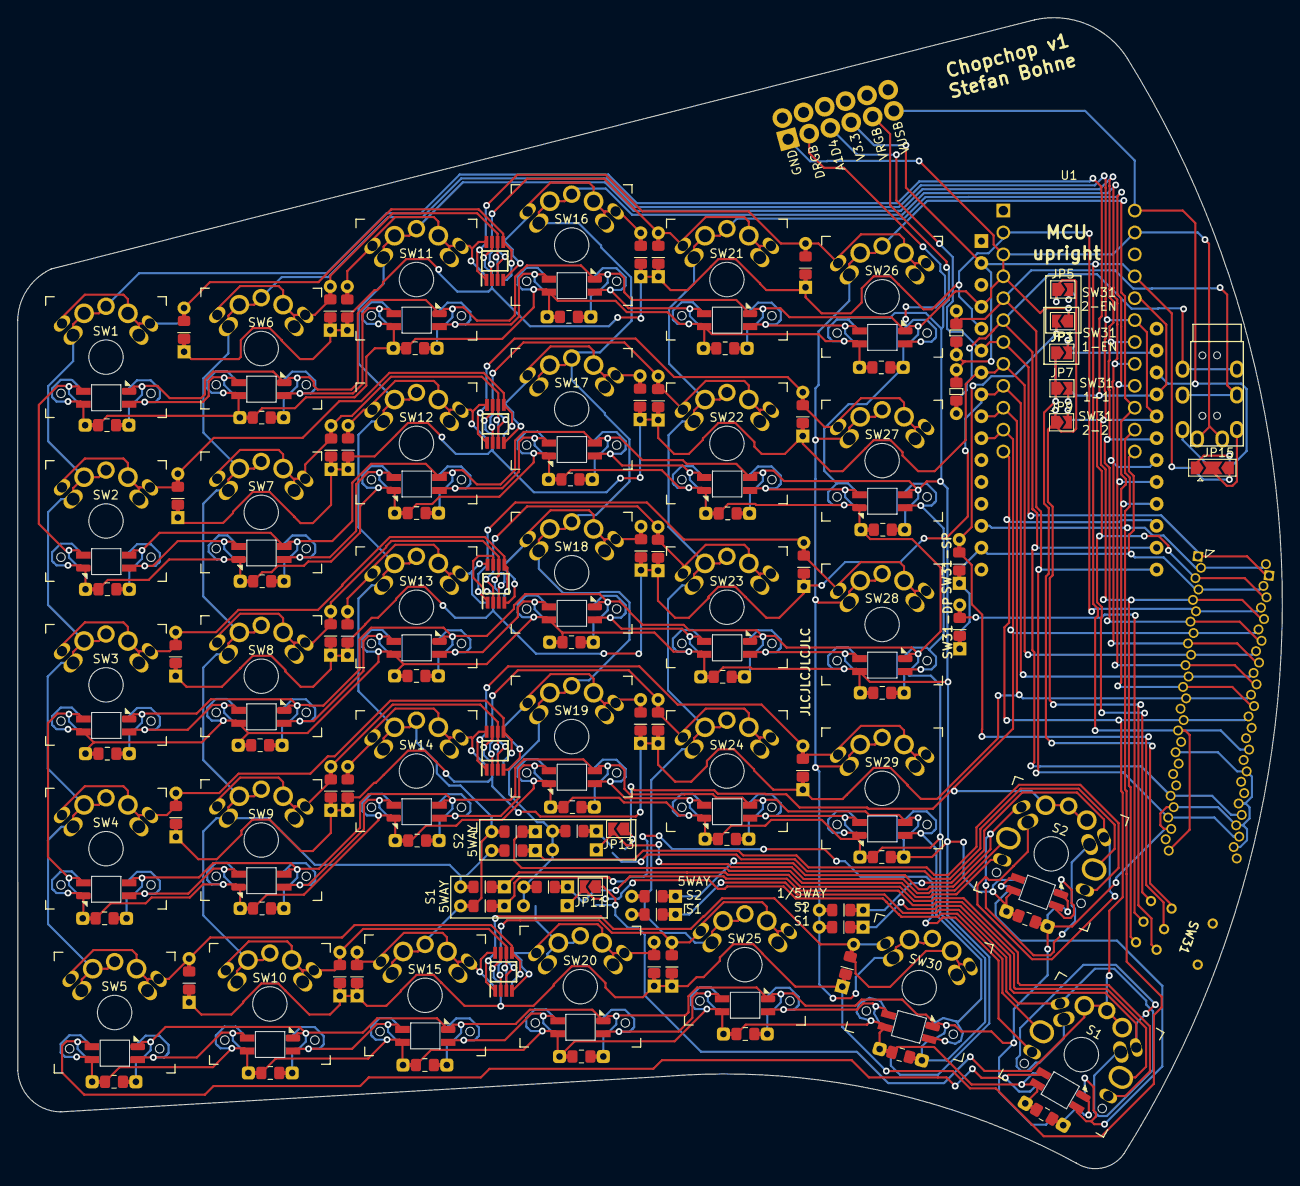
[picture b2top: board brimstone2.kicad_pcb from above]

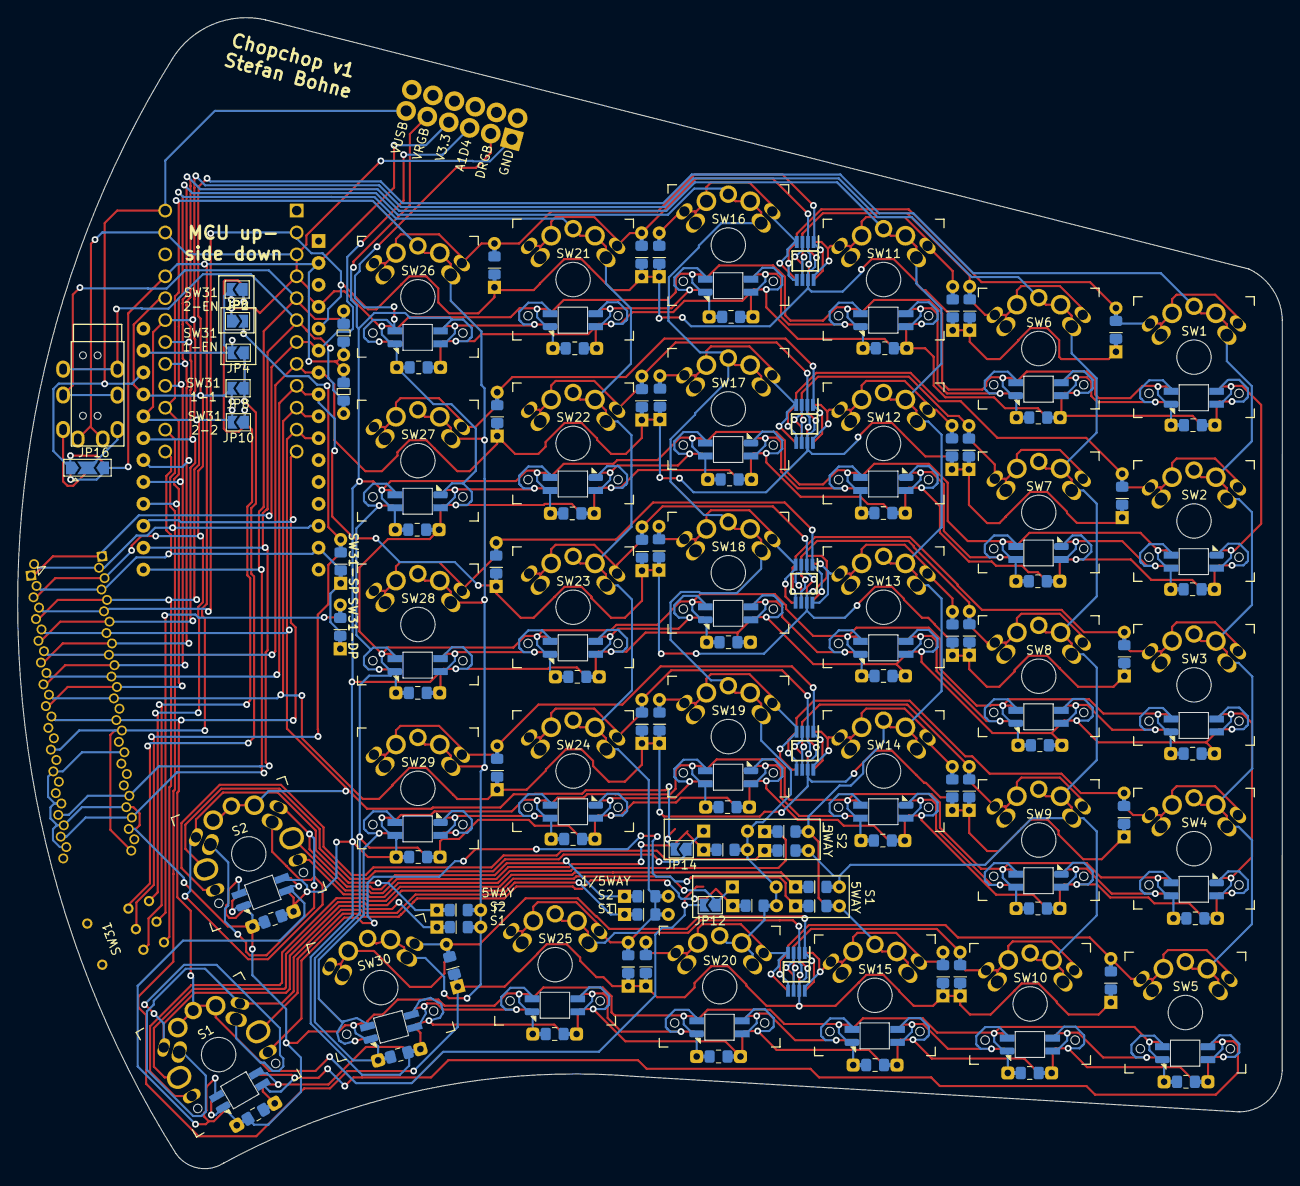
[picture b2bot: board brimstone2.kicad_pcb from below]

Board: 2 copper layers, 146.6 x 133.4 mm, 171 parts (12 on the bottom side), 102 nets.
